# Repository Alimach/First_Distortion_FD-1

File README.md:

# First_Distortion_FD-1
Реплика гитарной педали "Distortion +"

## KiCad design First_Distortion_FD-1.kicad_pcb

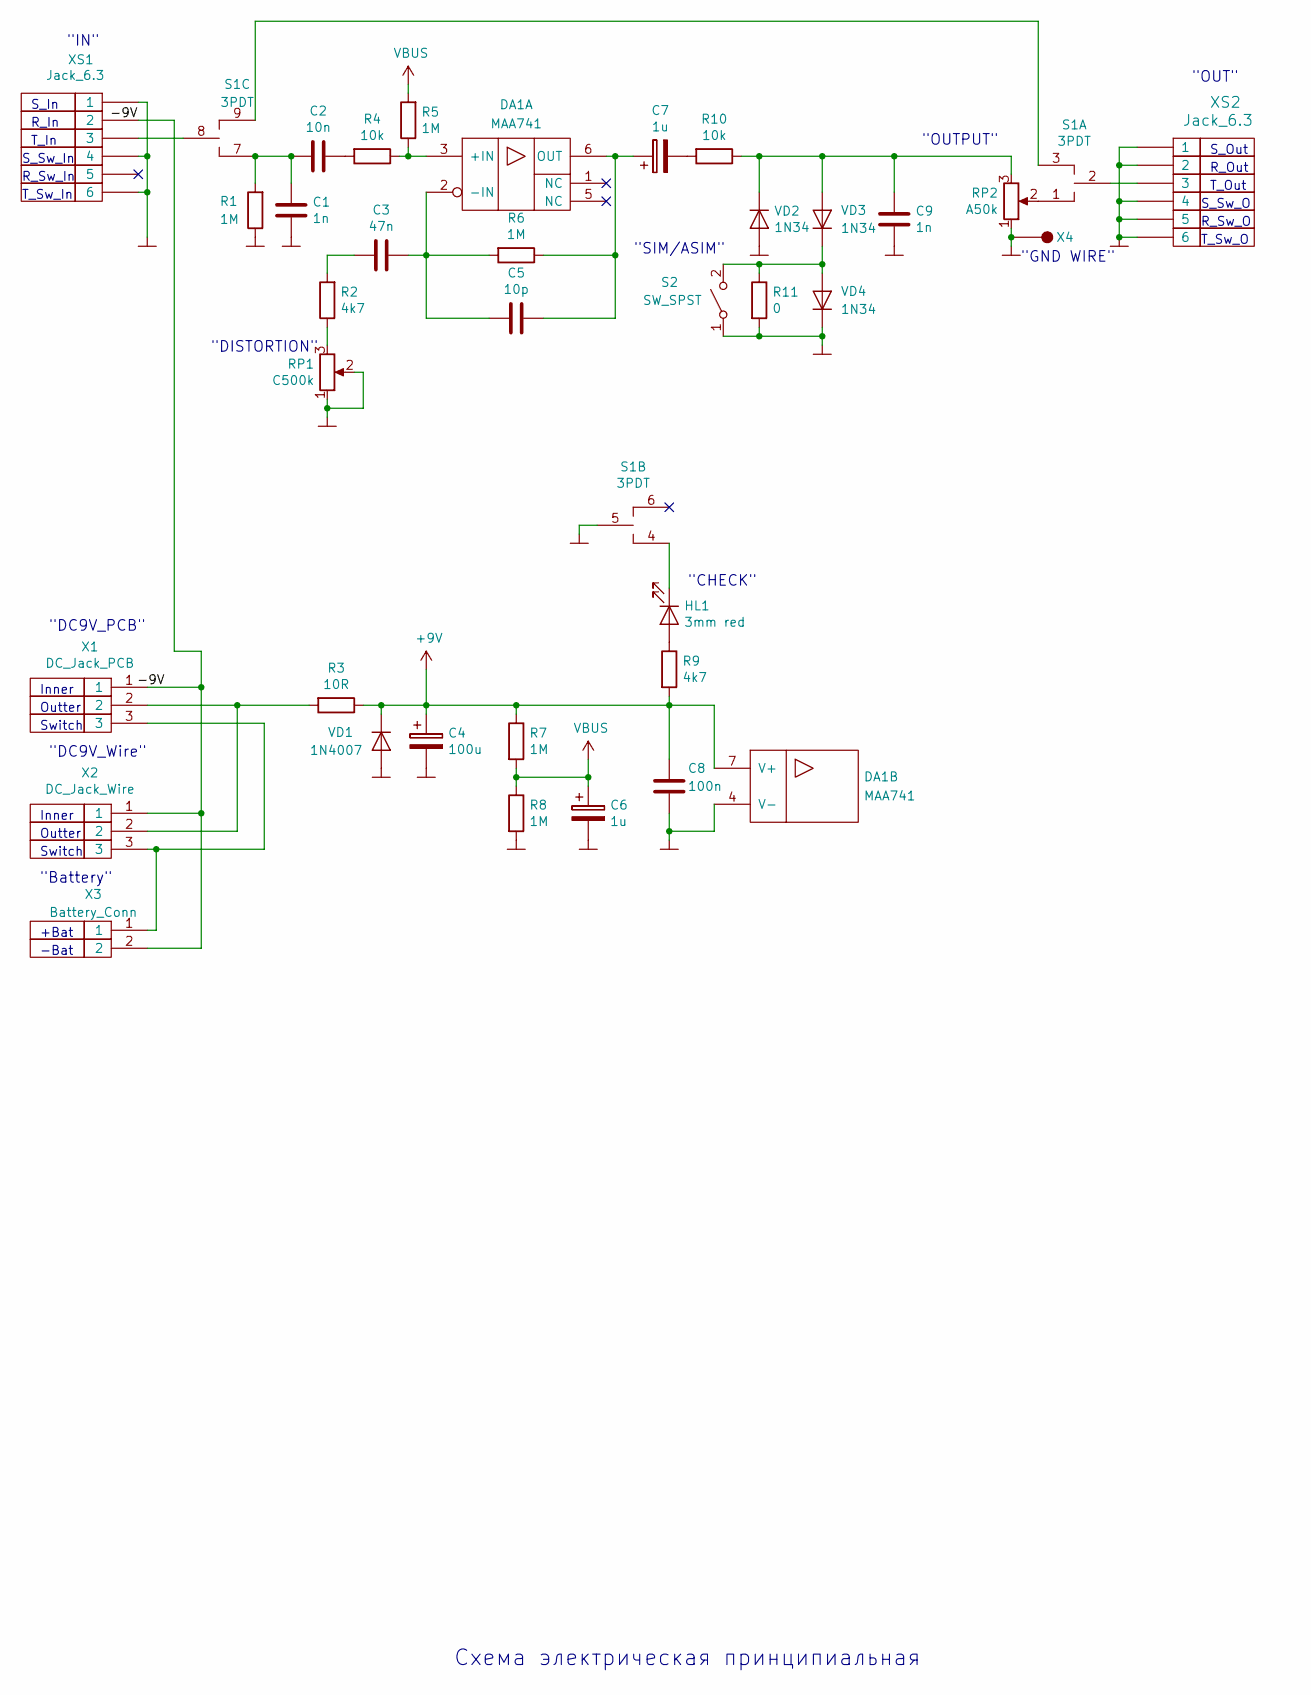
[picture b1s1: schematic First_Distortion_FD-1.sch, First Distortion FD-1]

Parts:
C1, C9: 1n; C_Rect_L7.0mm_W2.5mm_P5.00mm
C2: 10n; C_Rect_L7.0mm_W2.5mm_P5.00mm
C3: 47n; C_Rect_L7.0mm_W2.5mm_P5.00mm
C4: 100u; CP_Radial_D5.0mm_P2.50mm
C5: 10p; C_Disc_D5.0mm_W2.5mm_P5.00mm
C6, C7: 1u; CP_Radial_D5.0mm_P2.50mm
C8: 100n; C_Disc_D5.0mm_W2.5mm_P5.00mm
DA1: MAA741; DIP-8_W7.62mm_LongPads
HL1: 3mm red; LED_D3.0mm
R1, R5, R6, R7, R8: 1M; R_Axial_DIN0207_L6.3mm_D2.5mm_P7.62mm_Horizontal
R2, R9: 4k7; R_Axial_DIN0207_L6.3mm_D2.5mm_P7.62mm_Horizontal
R3: 10R; R_Axial_DIN0207_L6.3mm_D2.5mm_P7.62mm_Horizontal
R4, R10: 10k; R_Axial_DIN0207_L6.3mm_D2.5mm_P7.62mm_Horizontal
R11: 0; R_0805_HandSoldering
RP1: C500k; Alpha
RP2: A50k; Alpha
S1: 3PDT; 3PDT_Standart_Wire
S2: SW_SPST; Conn_x2
VD1: 1N4007; D_DO-41_SOD81_P7.62mm_Horizontal
VD2, VD3, VD4: 1N34; D_DO-41_SOD81_P7.62mm_Horizontal
X1: DC_Jack_PCB; BARREL_JACK
X2: DC_Jack_Wire; Fan_Pin_Header_Straight_1x03
X3: Battery_Conn; Conn_x2
X4: CON; SolderWirePad_single_1mmDrill
XS1, XS2: Jack_6.3; Jack_6.3_Stereo_2

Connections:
+9V: C4.1, C8.1, DA1.7 (V+), R3.1, R7.1, R9.2, VD1.1 (K)
/-9V: X1.1, X2.1, X3.2, XS1.2
GND: C1.1, C4.2, C6.2, C8.2, C9.1, DA1.4 (V-), R1.1, R8.2, R11.2, RP1.1, RP1.2, RP2.1, S1.5, S2.1 (A), VD1.2 (A), VD2.2 (A), VD4.1 (K), X4.1, XS1.1, XS1.4, XS1.6, XS2.1, XS2.2, XS2.4, XS2.5, XS2.6
unnamed: C1.2, C2.2, R1.2, S1.7
unnamed: C2.1, R4.2
unnamed: C3.1, C5.2, DA1.2 (-IN), R6.2
unnamed: C3.2, R2.2
unnamed: C5.1, C7.1, DA1.6 (OUT), R6.1
unnamed: C7.2, R10.2
unnamed: C9.2, R10.1, RP2.3, VD2.1 (K), VD3.2 (A)
unnamed: DA1.3 (+IN), R4.1, R5.1
unnamed: HL1.1 (K), S1.4
unnamed: HL1.2 (A), R9.1
unnamed: R2.1, RP1.3
unnamed: R3.2, X1.2, X2.2
unnamed: R11.1, S2.2 (B), VD3.1 (K), VD4.2 (A)
unnamed: RP2.2, S1.1
unnamed: S1.2, XS2.3
unnamed: S1.3, S1.9
unnamed: S1.8, XS1.3
unnamed: X1.3, X2.3, X3.1
VBUS: C6.1, R5.2, R7.2, R8.1

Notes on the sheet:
+Bat
-Bat
Inner
Outter
Switch
S_In
R_In
T_In
S_Sw_In
R_Sw_In
T_Sw_In
S_Out
R_Out
T_Out
S_Sw_O
R_Sw_O
T_Sw_O
"DISTORTION"
"OUTPUT"
"IN"
"OUT"
"GND WIRE"
"CHECK"
"SIM/ASIM"
Схема электрическая принципиальная
"DC9V_PCB"
"DC9V_Wire"
"Battery"

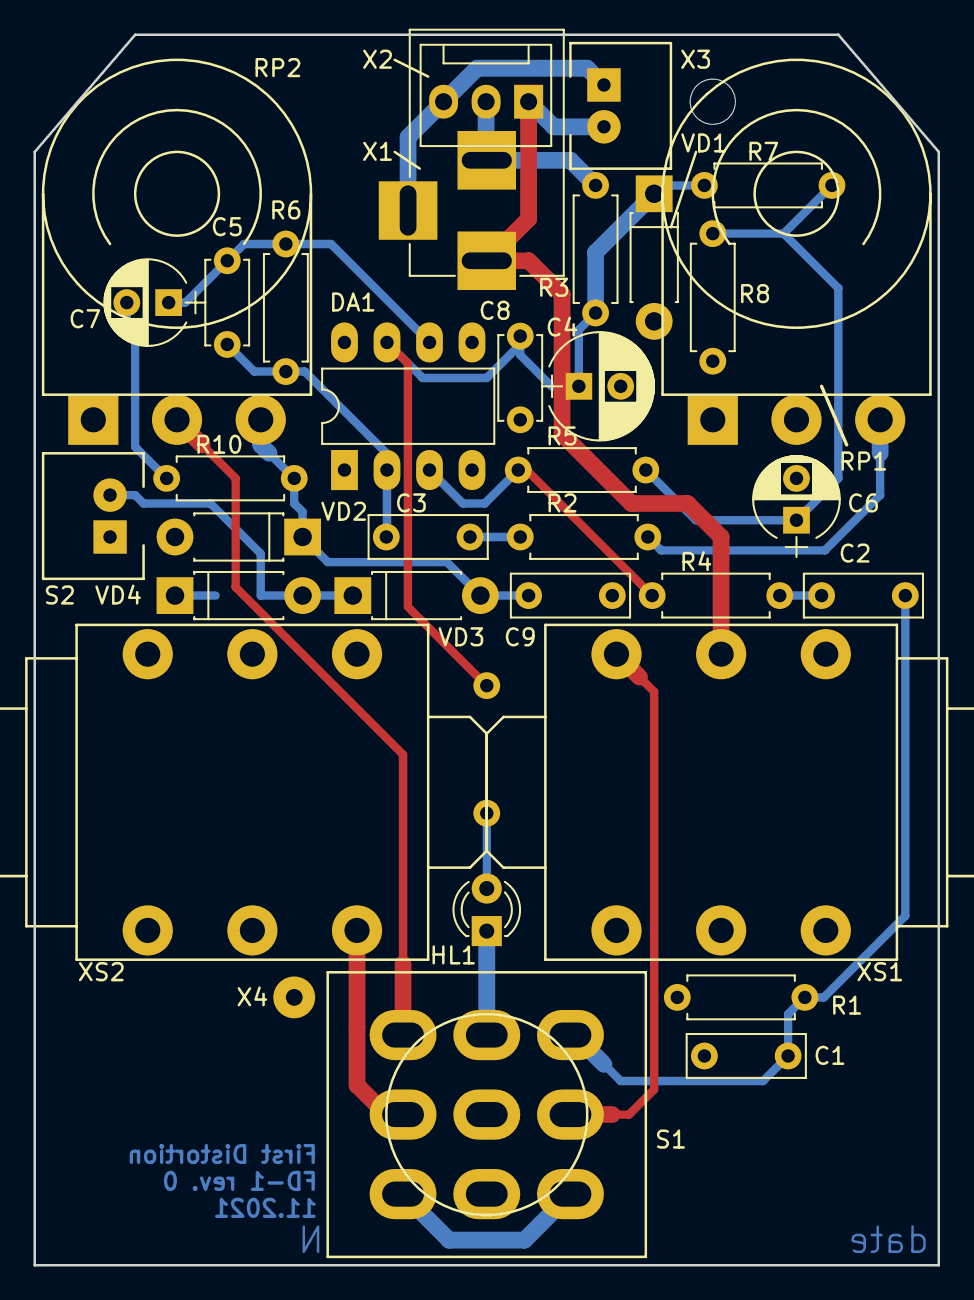
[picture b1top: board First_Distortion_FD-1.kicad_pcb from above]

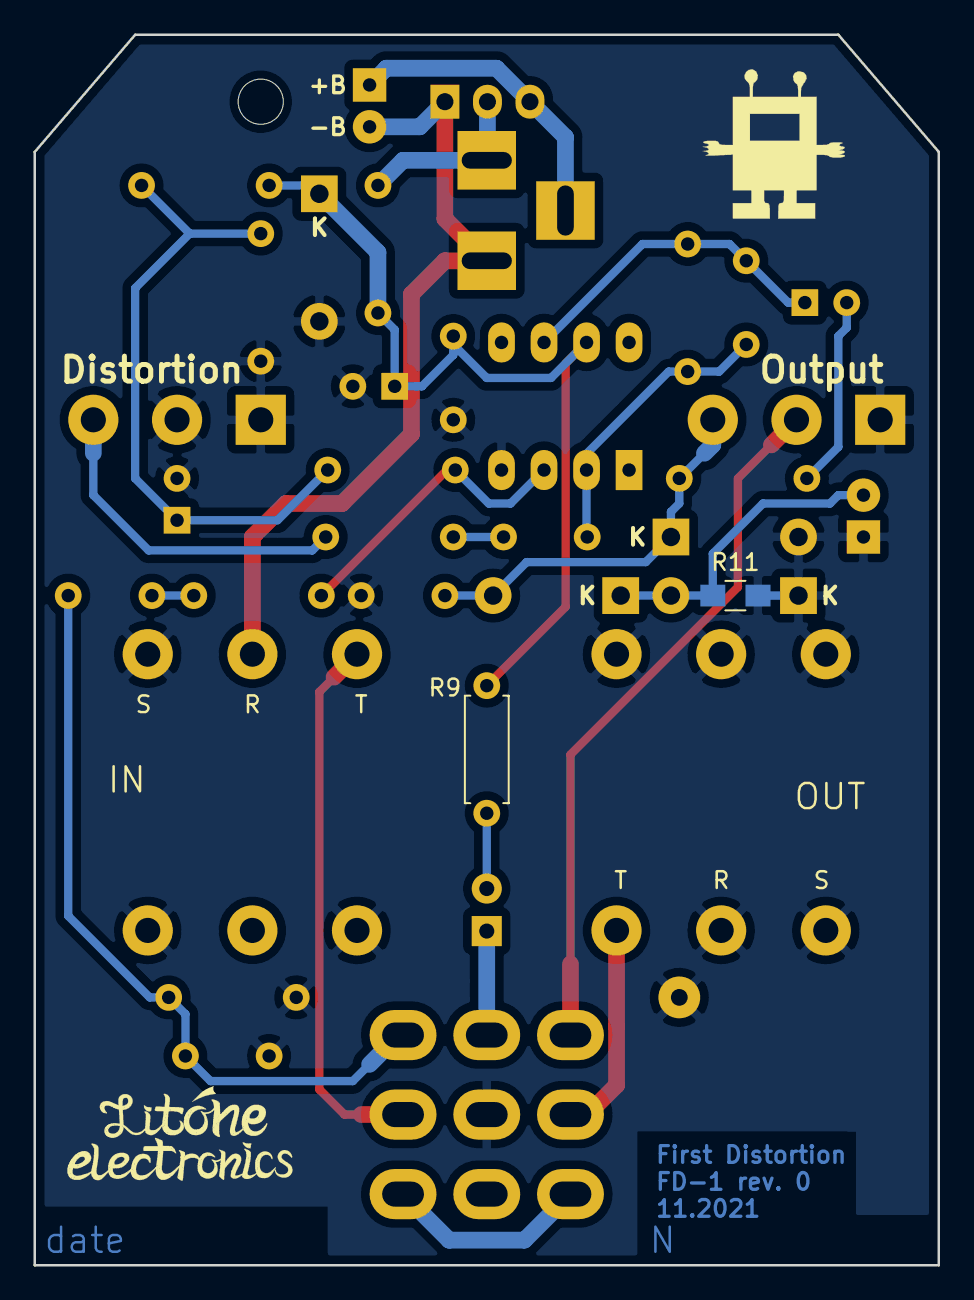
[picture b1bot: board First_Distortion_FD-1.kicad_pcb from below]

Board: 2 copper layers, 54.0 x 73.5 mm, 36 parts (2 on the bottom side), 22 nets.

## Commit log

2023-09-09 Исходная версия rev.0. Заказаны платы. Есть ошибка.
2023-09-09 Добавление чертежа развёртки корпуса для сверления
